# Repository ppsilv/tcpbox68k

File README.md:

## tcpbox68k
This is my MC68000 first project.

# Computer.

The idea behind this project is to develog a minicomputer as if I was in 1980.
I will try to use chips of that era except for memory because the memories of
that time were small in storage quantity.

I know that a concept of a minicomputer is not an exact science, so it is not
easy to reach a consensus on the subject, so I will use a definition that I found
very pertinent at the time of the reign of minicomputers. Since data storage
and memory were very expensive at that time, a minicomputer for its price had
to have many of these components.

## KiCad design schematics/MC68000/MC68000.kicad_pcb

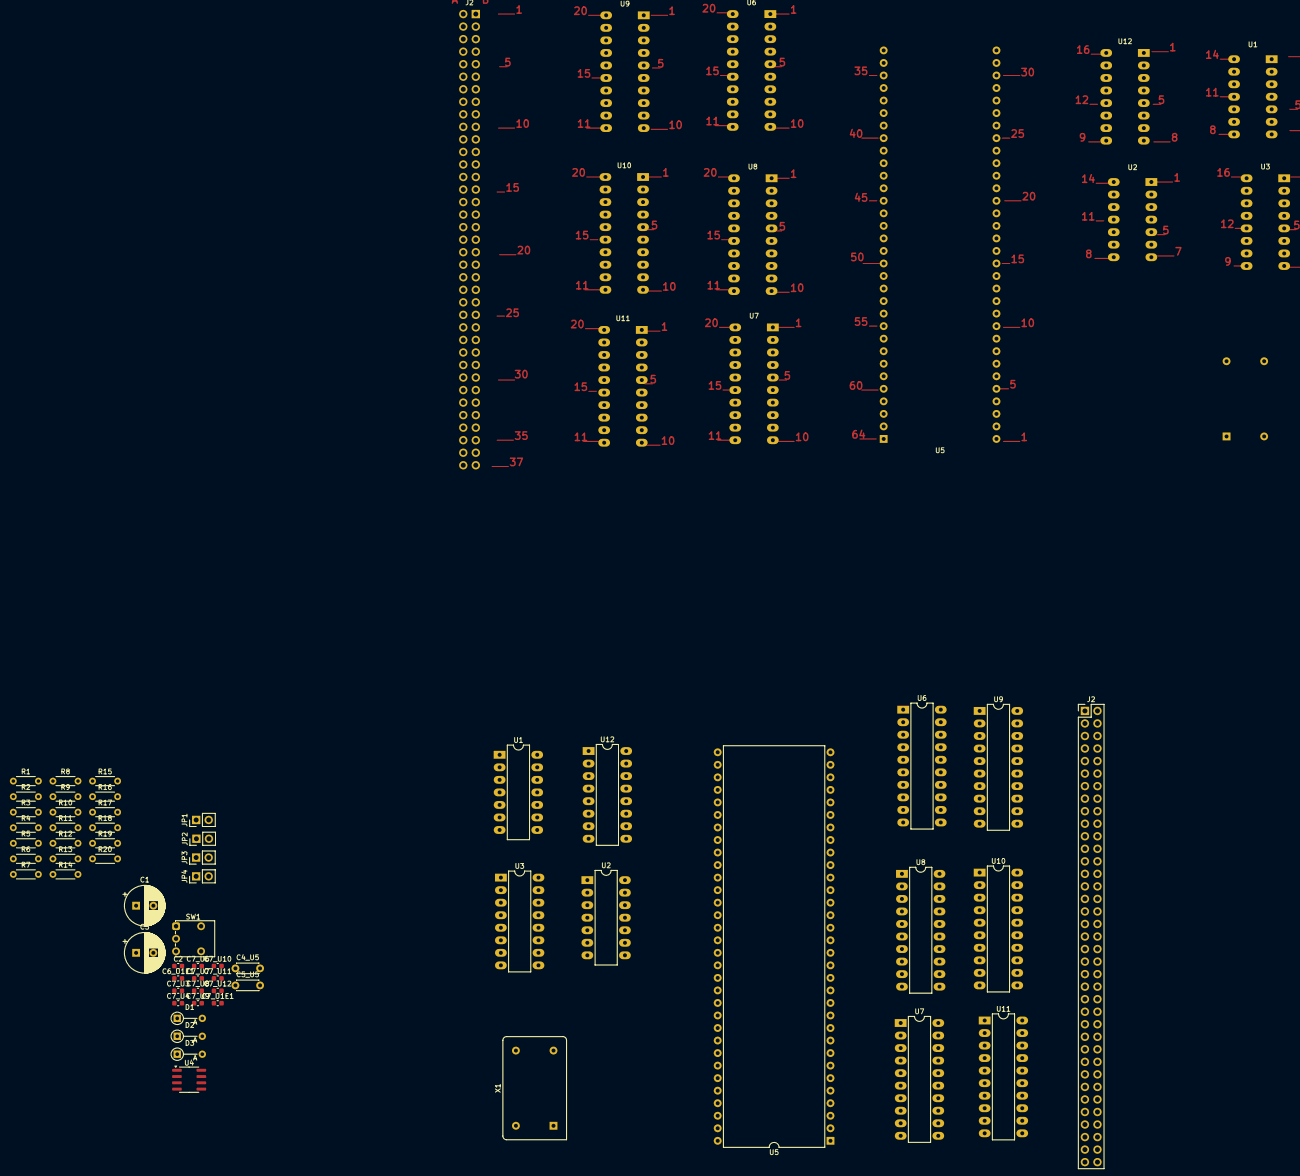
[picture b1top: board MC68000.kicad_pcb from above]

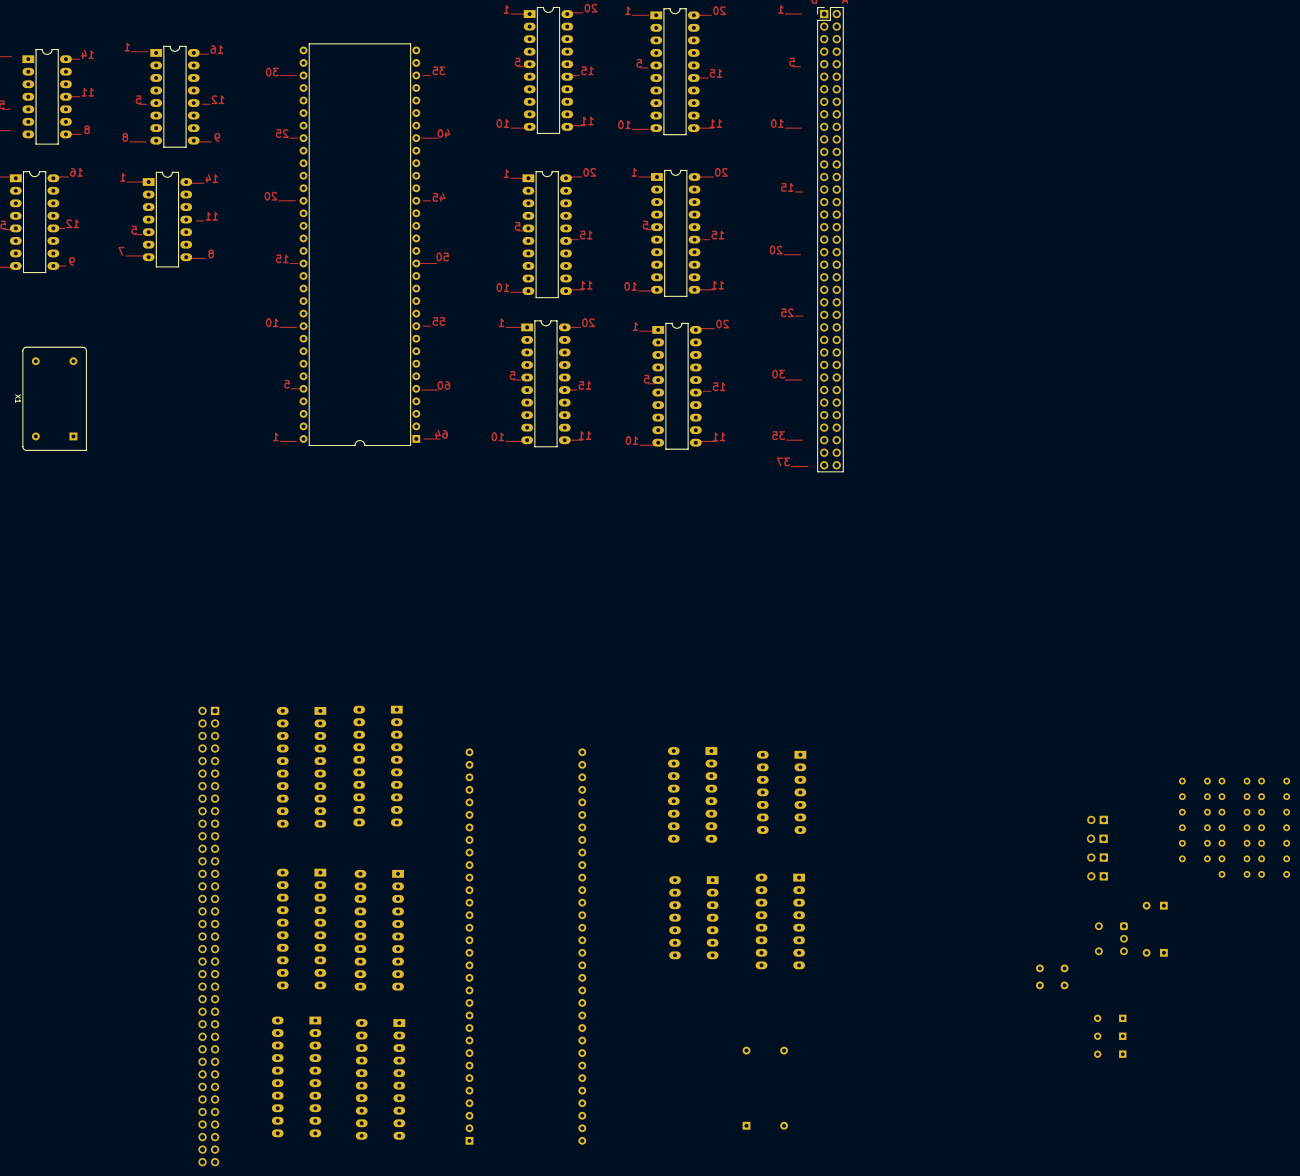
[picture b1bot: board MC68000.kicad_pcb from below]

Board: 2 copper layers, 71 parts (13 on the bottom side), 138 nets, no tracks yet.

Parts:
C1, C3: 1uf; CP_Radial_D8.0mm_P3.50mm
C2: 10nF; C_0603_1608Metric
C4_U5, C5_U5: 100nF; C_Disc_D4.3mm_W1.9mm_P5.00mm
C6_U1E1, C7_U1E1, C7_U3, C7_U4, C7_U6, C7_U7, C7_U8, C7_U9, C7_U10, C7_U11, C7_U12: 100nF; C_0603_1608Metric
D1: /RESET; D_DO-34_SOD68_P5.08mm_Vertical_AnodeUp
D2: /HALT; D_DO-34_SOD68_P5.08mm_Vertical_AnodeUp
D3: ON; D_DO-34_SOD68_P5.08mm_Vertical_AnodeUp
J2, J2#2: Conn_02x37_Row_Letter_Last; PinHeader_2x37_P2.54mm_Vertical
JP1, JP2: Jumper_2_Bridged; PinHeader_1x02_P2.54mm_Vertical
JP3, JP4: Jumper_2_Open; PinHeader_1x02_P2.54mm_Vertical
R1, R2, R3, R4, R7, R8, R9, R10, R11, R12, R13, R14, R15, R17: 10k; R_Axial_DIN0204_L3.6mm_D1.6mm_P5.08mm_Horizontal
R5, R6: 270k; R_Axial_DIN0204_L3.6mm_D1.6mm_P5.08mm_Horizontal
R16: 4K7; R_Axial_DIN0204_L3.6mm_D1.6mm_P5.08mm_Horizontal
R18, R19, R20: 470R; R_Axial_DIN0204_L3.6mm_D1.6mm_P5.08mm_Horizontal
SW1: Reset; SW_Push_1P2T_Vertical_E-Switch_800UDP8P1A1M6
U1, U1#2: 74LS00; CERDIP-14_W7.62mm_SideBrazed_LongPads
U2, U2#2: 74LS05; CERDIP-14_W7.62mm_SideBrazed_LongPads
U3, U3#2: 74LS161; CERDIP-16_W7.62mm_SideBrazed_LongPads
U4: ICM7555xB; SOIC-8_3.9x4.9mm_P1.27mm
U5, U5#2: 68000D; DIP-64_W22.86mm
U6, U6#2, U9, U9#2, U10, U10#2, U11, U11#2: 74LS244; CERDIP-20_W7.62mm_SideBrazed_LongPads
U7, U7#2, U8, U8#2: 74LS245; CERDIP-20_W7.62mm_SideBrazed_LongPads
U12, U12#2: 74LS148; CERDIP-16_W7.62mm_SideBrazed_LongPads
X1, X1#2: 16Mhz; Oscillator_DIP-14

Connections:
+5V: C4_U5.1, C5_U5.1, D1.1 (K), D2.1 (K), D3.1 (K), R1.1, R2.1, R3.1, R4.1, R5.1, R6.1, R7.1, R8.1, R9.1, R10.1, R11.1, R12.1, R13.1, R14.1, R15.1, R16.1, R17.1, U3.1 (~MR), U3.10 (CET), U3.16 (VCC), U3#2.1 (~MR), U3#2.10 (CET), U3#2.16 (VCC), U4.4 (R), U4.8 (VCC), U5.14 (VCC), U5.49 (VCC), U5#2.14 (VCC), U5#2.49 (VCC), U6.20 (VCC), U6#2.20 (VCC), U7.20 (VCC), U7#2.20 (VCC), U8.20 (VCC), U8#2.20 (VCC), U9.20 (VCC), U9#2.20 (VCC), U10.20 (VCC), U10#2.20 (VCC), U11.20 (VCC), U11#2.20 (VCC), U12.16 (VCC), U12#2.16 (VCC), X1.14 (Vcc), X1#2.14 (Vcc)
/CPU/D0: U5.5 (D0), U5#2.5 (D0), U7.18 (B0), U7#2.18 (B0)
/CPU/D1: U5.4 (D1), U5#2.4 (D1), U7.17 (B1), U7#2.17 (B1)
/CPU/D2: U5.3 (D2), U5#2.3 (D2), U7.16 (B2), U7#2.16 (B2)
/CPU/D3: U5.2 (D3), U5#2.2 (D3), U7.15 (B3), U7#2.15 (B3)
/CPU/D4: U5.1 (D4), U5#2.1 (D4), U7.14 (B4), U7#2.14 (B4)
/CPU/D5: U5.64 (D5), U5#2.64 (D5), U7.13 (B5), U7#2.13 (B5)
/CPU/D6: U5.63 (D6), U5#2.63 (D6), U7.12 (B6), U7#2.12 (B6)
/CPU/D7: U5.62 (D7), U5#2.62 (D7), U7.11 (B7), U7#2.11 (B7)
/CPU/D8: U5.61 (D8), U5#2.61 (D8), U8.18 (B0), U8#2.18 (B0)
/CPU/D9: U5.60 (D9), U5#2.60 (D9), U8.17 (B1), U8#2.17 (B1)
/CPU/D10: U5.59 (D10), U5#2.59 (D10), U8.16 (B2), U8#2.16 (B2)
/CPU/D11: U5.58 (D11), U5#2.58 (D11), U8.15 (B3), U8#2.15 (B3)
/CPU/D12: U5.57 (D12), U5#2.57 (D12), U8.14 (B4), U8#2.14 (B4)
/CPU/D13: U5.56 (D13), U5#2.56 (D13), U8.13 (B5), U8#2.13 (B5)
/CPU/D14: U5.55 (D14), U5#2.55 (D14), U8.12 (B6), U8#2.12 (B6)
/CPU/D15: U5.54 (D15), U5#2.54 (D15), U8.11 (B7), U8#2.11 (B7)
/CPU/FC0: U5.28 (FC0), U5#2.28 (FC0), U6.11 (I0b), U6#2.11 (I0b)
/CPU/FC1: U5.27 (FC1), U5#2.27 (FC1), U6.13 (I1b), U6#2.13 (I1b)
/CPU/FC2: U5.26 (FC2), U5#2.26 (FC2), U6.15 (I2b), U6#2.15 (I2b)
/CPU/IPL0: R15.2, U5.25 (IPL0), U5#2.25 (IPL0), U12.9 (S0), U12#2.9 (S0)
/CPU/IPL1: R14.2, U5.24 (IPL1), U5#2.24 (IPL1), U12.7 (S1), U12#2.7 (S1)
/CPU/IPL2: R13.2, U5.23 (IPL2), U5#2.23 (IPL2), U12.6 (S2), U12#2.6 (S2)
/CPU/IRQ1: U12.11 (I1), U12#2.11 (I1)
/CPU/IRQ2: U12.12 (I2), U12#2.12 (I2)
/CPU/IRQ3: U12.13 (I3), U12#2.13 (I3)
/CPU/IRQ4: U12.1 (I4), U12#2.1 (I4)
/CPU/IRQ5: U12.2 (I5), U12#2.2 (I5)
/CPU/IRQ6: U12.3 (I6), U12#2.3 (I6)
/CPU/IRQ7: U12.4 (I7), U12#2.4 (I7)
/CPU/LDS: U5.8 (LDS), U5#2.8 (LDS)
/CPU/R/W: U5.9 (R/W), U5#2.9 (R/W), U6.17 (I3b), U6#2.17 (I3b), U7.1 (A->B), U7#2.1 (A->B), U8.1 (A->B), U8#2.1 (A->B)
/CPU/UDS: U5.7 (UDS), U5#2.7 (UDS)
/CPU/addr1: U5.29 (A1), U5#2.29 (A1), U9.2 (I0a), U9#2.2 (I0a)
/CPU/addr2: U5.30 (A2), U5#2.30 (A2), U9.4 (I1a), U9#2.4 (I1a)
/CPU/addr3: U5.31 (A3), U5#2.31 (A3), U9.6 (I2a), U9#2.6 (I2a)
/CPU/addr4: U5.32 (A4), U5#2.32 (A4), U9.8 (I3a), U9#2.8 (I3a)
/CPU/addr5: U5.33 (A5), U5#2.33 (A5), U9.11 (I0b), U9#2.11 (I0b)
/CPU/addr6: U5.34 (A6), U5#2.34 (A6), U9.13 (I1b), U9#2.13 (I1b)
/CPU/addr7: U5.35 (A7), U5#2.35 (A7), U9.15 (I2b), U9#2.15 (I2b)
/CPU/addr8: U5.36 (A8), U5#2.36 (A8), U9.17 (I3b), U9#2.17 (I3b)
/CPU/addr9: U5.37 (A9), U5#2.37 (A9), U10.2 (I0a), U10#2.2 (I0a)
/CPU/addr10: U5.38 (A10), U5#2.38 (A10), U10.4 (I1a), U10#2.4 (I1a)
/CPU/addr11: U5.39 (A11), U5#2.39 (A11), U10.6 (I2a), U10#2.6 (I2a)
/CPU/addr12: U5.40 (A12), U5#2.40 (A12), U10.8 (I3a), U10#2.8 (I3a)
/CPU/addr13: U5.41 (A13), U5#2.41 (A13), U10.11 (I0b), U10#2.11 (I0b)
/CPU/addr14: U5.42 (A14), U5#2.42 (A14), U10.13 (I1b), U10#2.13 (I1b)
/CPU/addr15: U5.43 (A15), U5#2.43 (A15), U10.15 (I2b), U10#2.15 (I2b)
/CPU/addr16: U5.44 (A16), U5#2.44 (A16), U10.17 (I3b), U10#2.17 (I3b)
/CPU/addr17: U5.45 (A17), U5#2.45 (A17), U11.2 (I0a), U11#2.2 (I0a)
/CPU/addr18: U5.46 (A18), U5#2.46 (A18), U11.4 (I1a), U11#2.4 (I1a)
/CPU/addr19: U5.47 (A19), U5#2.47 (A19), U11.6 (I2a), U11#2.6 (I2a)
/CPU/addr20: U5.48 (A20), U5#2.48 (A20), U11.8 (I3a), U11#2.8 (I3a)
/CPU/addr21: U5.50 (A21), U5#2.50 (A21), U11.11 (I0b), U11#2.11 (I0b)
/CPU/addr22: U5.51 (A22), U5#2.51 (A22), U11.13 (I1b), U11#2.13 (I1b)
/CPU/addr23: U5.52 (A23), U5#2.52 (A23), U11.15 (I2b), U11#2.15 (I2b)
/CPU/bA1: U9.18 (O0a), U9#2.18 (O0a)
/CPU/bA2: U9.16 (O1a), U9#2.16 (O1a)
/CPU/bA3: U9.14 (O2a), U9#2.14 (O2a)
/CPU/bA4: U9.12 (O3a), U9#2.12 (O3a)
/CPU/bA5: U9.9 (O0b), U9#2.9 (O0b)
/CPU/bA6: U9.7 (O1b), U9#2.7 (O1b)
/CPU/bA7: U9.5 (O2b), U9#2.5 (O2b)
/CPU/bA8: U9.3 (O3b), U9#2.3 (O3b)
/CPU/bA9: U10.18 (O0a), U10#2.18 (O0a)
/CPU/bA10: U10.16 (O1a), U10#2.16 (O1a)
/CPU/bA11: U10.14 (O2a), U10#2.14 (O2a)
/CPU/bA12: U10.12 (O3a), U10#2.12 (O3a)
/CPU/bA13: U10.9 (O0b), U10#2.9 (O0b)
/CPU/bA14: U10.7 (O1b), U10#2.7 (O1b)
/CPU/bA15: U10.5 (O2b), U10#2.5 (O2b)
/CPU/bA16: U10.3 (O3b), U10#2.3 (O3b)
/CPU/bA17: U11.18 (O0a), U11#2.18 (O0a)
/CPU/bA18: U11.16 (O1a), U11#2.16 (O1a)
/CPU/bA19: U11.14 (O2a), U11#2.14 (O2a)
/CPU/bA20: U11.12 (O3a), U11#2.12 (O3a)
/CPU/bA21: U11.9 (O0b), U11#2.9 (O0b)
/CPU/bA22: U11.7 (O1b), U11#2.7 (O1b)
/CPU/bA23: U11.5 (O2b), U11#2.5 (O2b)
/CPU/bD0: U7.2 (A0), U7#2.2 (A0)
/CPU/bD1: U7.3 (A1), U7#2.3 (A1)
/CPU/bD2: U7.4 (A2), U7#2.4 (A2)
/CPU/bD3: U7.5 (A3), U7#2.5 (A3)
/CPU/bD4: U7.6 (A4), U7#2.6 (A4)
/CPU/bD5: U7.7 (A5), U7#2.7 (A5)
/CPU/bD6: U7.8 (A6), U7#2.8 (A6)
/CPU/bD7: U7.9 (A7), U7#2.9 (A7)
/CPU/bD8: U8.2 (A0), U8#2.2 (A0)
/CPU/bD9: U8.3 (A1), U8#2.3 (A1)
/CPU/bD10: U8.4 (A2), U8#2.4 (A2)
/CPU/bD11: U8.5 (A3), U8#2.5 (A3)
/CPU/bD12: U8.6 (A4), U8#2.6 (A4)
/CPU/bD13: U8.7 (A5), U8#2.7 (A5)
/CPU/bD14: U8.8 (A6), U8#2.8 (A6)
/CPU/bD15: U8.9 (A7), U8#2.9 (A7)
/CPU/bE: U6.12 (O3a), U6#2.12 (O3a)
/CPU/bFC0: U6.9 (O0b), U6#2.9 (O0b)
/CPU/bFC1: U6.7 (O1b), U6#2.7 (O1b)
/CPU/bFC2: U6.5 (O2b), U6#2.5 (O2b)
/CPU/bR/W: U6.3 (O3b), U6#2.3 (O3b)
/CPU//AS: U5.6 (AS), U5#2.6 (AS), U11.17 (I3b), U11#2.17 (I3b)
/CPU//BERR: R7.2, U5.22 (BERR), U5#2.22 (BERR)
/CPU//BG: U5.11 (BG), U5#2.11 (BG)
/CPU//BGACK: R12.2, U2.5, U2#2.5, U5.12 (BGACK), U5#2.12 (BGACK)
/CPU//BR: R10.2, U5.13 (BR), U5#2.13 (BR)
/CPU//DTACK: R17.2, U3.11 (Q3), U3#2.11 (Q3), U5.10 (DTACK), U5#2.10 (DTACK)
/CPU//E: U5.20 (E), U5#2.20 (E), U6.8 (I3a), U6#2.8 (I3a)
/CPU//HALT: R11.2, U2.4, U2.9, U2#2.4, U2#2.9, U5.17 (HALT), U5#2.17 (HALT)
/CPU//LDS: U6.4 (I1a), U6#2.4 (I1a)
/CPU//RESET: R9.2, R18.2, U2.2, U2#2.2, U5.18 (RESET), U5#2.18 (RESET)
/CPU//UDS: U6.2 (I0a), U6#2.2 (I0a)
/CPU//VMA: U5.19 (VMA), U5#2.19 (VMA), U6.6 (I2a), U6#2.6 (I2a)
/CPU//VPA: R8.2, U5.21 (VPA), U5#2.21 (VPA)
/CPU//bAS: U11.3 (O3b), U11#2.3 (O3b)
/CPU//bLDS: U6.16 (O1a), U6#2.16 (O1a)
/CPU//bUDS: U6.18 (O0a), U6#2.18 (O0a)
/CPU//bVMA: U6.14 (O2a), U6#2.14 (O2a)
CLK: U3.2 (CP), U3#2.2 (CP)
GND: C1.2, C2.2, C3.2, C4_U5.2, C5_U5.2, JP1.1 (A), JP2.1 (A), JP3.1 (A), JP4.1 (A), R20.2, SW1.1, U3.8 (GND), U3#2.8 (GND), U4.1 (GND), U5.16 (GND), U5.53 (GND), U5#2.16 (GND), U5#2.53 (GND), U6.10 (GND), U6#2.10 (GND), U7.10 (GND), U7.19 (CE), U7#2.10 (GND), U7#2.19 (CE), U8.10 (GND), U8.19 (CE), U8#2.10 (GND), U8#2.19 (CE), U9.10 (GND), U9#2.10 (GND), U10.10 (GND), U10#2.10 (GND), U11.10 (GND), U11#2.10 (GND), U12.5 (EI), U12.8 (GND), U12.10 (IO), U12#2.5 (EI), U12#2.8 (GND), U12#2.10 (IO), X1.7 (GND), X1#2.7 (GND)
unnamed: D1.2 (A), R18.1
unnamed: D2.2 (A), R19.1
unnamed: D3.2 (A), R20.1
unnamed: JP1.2 (B), R1.2, U3.3 (D0), U3#2.3 (D0)
unnamed: JP2.2 (B), R2.2, U3.4 (D1), U3#2.4 (D1)
unnamed: JP3.2 (B), R3.2, U3.5 (D2), U3#2.5 (D2)
unnamed: JP4.2 (B), R4.2, U3.6 (D3), U3#2.6 (D3)
unnamed: R19.2, U2.8, U2#2.8
unnamed: C6_U1E1.2, C7_U1E1.2, C7_U3.2, C7_U4.2, C7_U6.2, C7_U7.2, C7_U8.2, C7_U9.2, C7_U10.2, C7_U11.2, C7_U12.2, U1.7 (GND), U1#2.7 (GND), U2.7 (GND), U2#2.7 (GND)
unnamed: C6_U1E1.1, C7_U1E1.1, C7_U3.1, C7_U4.1, C7_U6.1, C7_U7.1, C7_U8.1, C7_U9.1, C7_U10.1, C7_U11.1, C7_U12.1, U1.14 (VCC), U1#2.14 (VCC), U2.14 (VCC), U2#2.14 (VCC)
unnamed: U1.3, U1#2.3, U3.7 (CEP), U3.9 (~PE), U3#2.7 (CEP), U3#2.9 (~PE)
unnamed: C2.1, U4.5 (CV)
unnamed: C3.1, R6.2, U4.6 (THR), U4.7 (DIS)
unnamed: U2.1, U2.3, U2#2.1, U2#2.3, U4.3 (Q)
unnamed: C1.1, R5.2, SW1.2, U4.2 (TR)
unnamed: U5.15 (CLK), U5#2.15 (CLK), X1.8 (OUT), X1#2.8 (OUT)
unnamed: R16.2, U2.6, U2#2.6, U6.1 (OEa), U6.19 (OEb), U6#2.1 (OEa), U6#2.19 (OEb), U9.1 (OEa), U9.19 (OEb), U9#2.1 (OEa), U9#2.19 (OEb), U10.1 (OEa), U10.19 (OEb), U10#2.1 (OEa), U10#2.19 (OEb), U11.1 (OEa), U11.19 (OEb), U11#2.1 (OEa), U11#2.19 (OEb)
/RAM_CS: U1.2, U1#2.2
/ROM_CE: U1.1, U1#2.1

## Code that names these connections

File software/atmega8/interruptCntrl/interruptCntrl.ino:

#include <avr/io.h>
#include <util/atomic.h>
#include <util/delay.h>

//When cpu say FC0,FC1 and FC2  = 1,1,1 but no interrupt active.
#define CPU_INT_ACK_WRONG     0x80
//When arrive a irq resquest but we have one active irq in curse
#define IRQ_REQUEST_LOST      0x81
//ACK sem interrupção
#define ACK_WITHOUT_INT       0x82
//Irq <level> must be released
#define IRQ_MUST_BE_RELEASED  0x83

// Definições dos pinos IPL no PORTB
#define IPL0  PC0
#define IPL1  PC1  
#define IPL2  PC2
#define IPL_MASK ((1 << IPL0) | (1 << IPL1) | (1 << IPL2))

// Definições dos pinos de IRQ no PORTD
#define IRQ1_PIN  PD2
#define IRQ2_PIN  PD3
#define IRQ3_PIN  PD4
#define IRQ4_PIN  PD5
#define IRQ5_PIN  PD6
#define IRQ7_PIN  PD7
#define ALL_IRQ_MASK ((1<<IRQ1_PIN)|(1<<IRQ2_PIN)|(1<<IRQ3_PIN)|(1<<IRQ4_PIN)|(1<<IRQ5_PIN)|(1<<IRQ7_PIN))

#define TIMEOUT  1000
long timer1=millis()+100;
long timer2=millis()+TIMEOUT;

#define NOT_ACTIVE 7
unsigned char irq_s[8]={NOT_ACTIVE,NOT_ACTIVE,NOT_ACTIVE,NOT_ACTIVE,NOT_ACTIVE,NOT_ACTIVE,NOT_ACTIVE,NOT_ACTIVE};
// Variáveis globais
volatile uint8_t active_irq = NOT_ACTIVE;

#define LED_PIN PB5  // Exemplo: LED no PB5 (ajuste conforme seu hardware)
#define LED_PORT PORTB

// Configuração dos ports
void setup_ports() {
    // Configurar PB0-PB2 como saídas (IPL0-IPL2) + VPA_PIN
    DDRC |= (1 << IPL0) | (1 << IPL1) | (1 << IPL2) ;
    // VPA inicialmente inativo    
    PORTC |=  (1 << IPL0) | (1 << IPL1) | (1 << IPL2) ;  
    
    // Configurar PB1 como saída (OC1A - Debug) LED
    DDRB |= (1 << PB1)|(1 << PB5)  ;

    // Configura PD0-PD5 como entradas com pull-up
    DDRD &= ~ALL_IRQ_MASK;
    PORTD |= ALL_IRQ_MASK;    
}

void setup_timer1() {
    TCCR1A = (1 << COM1A0);    // Toggle OC1A on compare match
    TCCR1B = (1 << WGM12) | (1 << CS11);  // CTC mode, prescaler 8
    OCR1A = 500;              // 1ms period
    TIMSK |= (1 << OCIE1A);    // Habilitar interrupção
}

volatile uint32_t ms_counter = 0;

ISR(TIMER1_COMPA_vect) {
  ms_counter++;
  //start_irq(1);  // Gera IRQ nível 6
}

void setup_timer2() {  // ATMega8 usa Timer2, não Timer0
    // Configurar Timer2 para CTC mode
    TCCR2 = (1 << WGM21);              // CTC mode
    OCR2 = 78;                         // 50us @ 16MHz/8
    TCCR2 |= (1 << CS21);              // Prescaler 8
    TIMSK |= (1 << OCIE2);             // Enable interrupt
}

ISR(TIMER2_COMP_vect) {

}
void setup_fc_interrupt() {
    // Configurar INT0 para FALLING EDGE (transição 1→0)
    MCUCR |= (1 << ISC01);      // Falling edge generates interrupt  
    MCUCR &= ~(1 << ISC00);     // Clear ISC00 bit
    GICR |= (1 << INT0);        // Enable INT0
}

ISR(INT0_vect) {
  irq_s[active_irq]=NOT_ACTIVE;
        __asm__ volatile("nop");   // +125ns - 1 ciclo
        __asm__ volatile("nop");   // +125ns - 1 ciclo  
        __asm__ volatile("nop");   // +125ns - 1 ciclo  
        __asm__ volatile("nop");   // +125ns - 1 ciclo
        __asm__ volatile("nop");   // +125ns - 1 ciclo  
        __asm__ volatile("nop");   // +125ns - 1 ciclo        
  PORTC = (PORTC & 0xF8);  //Limpa
  PORTC = PORTC | NOT_ACTIVE;   //seta
}

uint8_t check_irq_pins_status() {
    return (~PIND) & ALL_IRQ_MASK;
}



uint8_t get_irq_started() {
    uint8_t status = check_irq_pins_status();
    if (status & (1<<IRQ7_PIN)) return 0;
    if (status & (1<<IRQ5_PIN)) return 2;
    if (status & (1<<IRQ4_PIN)) return 3;
    if (status & (1<<IRQ3_PIN)) return 4;
    if (status & (1<<IRQ2_PIN)) return 5;
    if (status & (1<<IRQ1_PIN)) return 6;
    return NOT_ACTIVE;
}

// ✅ Função set_ipl CORRIGIDA
void set_ipl(uint8_t level) {
  level &= 0x07;
  //PORTC = (PORTC & 0xF8);  //Limpa 
  //PORTC = PORTC | level;   //seta
  PORTC = (PORTC & 0xF8) | level;  // Seta nível

  //      __asm__ volatile("nop");   // +125ns - 1 ciclo  
  //      __asm__ volatile("nop");   // +125ns - 1 ciclo
  //      __asm__ volatile("nop");   // +125ns - 1 ciclo  
  //      __asm__ volatile("nop");   // +125ns - 1 ciclo        
  //      __asm__ volatile("nop");   // +125ns - 1 ciclo  
  //      __asm__ volatile("nop");   // +125ns - 1 ciclo
  //      __asm__ volatile("nop");   // +125ns - 1 ciclo  
  //      __asm__ volatile("nop");   // +125ns - 1 ciclo        
  //      __asm__ volatile("nop");   // +125ns - 1 ciclo  
  //      __asm__ volatile("nop");   // +125ns - 1 ciclo
  //      __asm__ volatile("nop");   // +125ns - 1 ciclo  
  //      __asm__ volatile("nop");   // +125ns - 1 ciclo        
  // ⏰ Timing calibrado manualmente
    __asm__ volatile("nop\nnop\nnop\nnop\nnop\nnop\nnop\nnop\nnop\nnop\nnop\nnop");

  PORTC = (PORTC & 0xF8) | NOT_ACTIVE;  // Limpa ANTES do retrigger

  //PORTC = (PORTC & 0xF8);  //Limpa
  //PORTC = PORTC | NOT_ACTIVE;   //seta
  _delay_us(500);
  irq_s[active_irq]=NOT_ACTIVE;
  

}

void start_irq(uint8_t new_irq){
  if(new_irq == NOT_ACTIVE) return; //excesso de zelo quando estiver funcionando corretamente tirar isso daqui
  if (new_irq < 7 && irq_s[new_irq] == NOT_ACTIVE) {
    active_irq = new_irq;
    irq_s[active_irq]=active_irq;
    set_ipl(active_irq);
  }
}

void setup(){
  Serial.begin(9600);
  Serial.println("Teste do gerenciador de interrupção 1.0"); 
  setup_ports();

  //Setup interrups
  setup_timer1();
  //setup_timer2();

  sei();
  pinMode(LED_BUILTIN, OUTPUT);    
  timer1=millis()+TIMEOUT;
  //delay(5000); // 5 segundo
}


void loop() {

  while(1) {
    // 1️⃣ Verificação SÍNCRONA das IRQs
    start_irq(get_irq_started());

    //Activity led
    if ( (millis() > timer1) ){
      timer1=millis()+100;
      LED_PORT ^= (1 << LED_PIN);  // toggle LED
    }
  }
}

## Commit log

2025-07-04 Update...
2025-07-04 CPU schematic finished...
2025-07-09 cleanup zips and added memory map equations for pld
2025-07-12 added schemati for cpu without buffers
2025-07-13 Cpu's board tested
2025-07-14 Added test_led.asm
2025-07-16 remove doc dir
2025-07-17 update ebooks
2025-07-19 Monitor compiled success
2025-07-19 update makefile
2025-07-19 lib math added
2025-07-19 lib math removed
2025-07-21 update memoria rom executando codigo
2025-07-21 Leds blinking...
2025-07-22 Ram memory test 2 OK
2025-07-25 Uart reading writing with counter.asm
2025-07-25 Version 0.10 4 uarts running...
2025-07-25 Error's log updated...
2025-07-26 Compilando com linker
2025-07-28 Reading hexa values
2025-07-29 change bin name
2025-07-29 Build: 2025-07-29 17:28:19
2025-07-29 Update Makefile cosmetic things
2025-07-30 Terminal serial...
2025-07-31 Terminal serial
2025-08-01 Terminal totalmente debugado
2025-08-01 Refactoring of pdterm
2025-08-01 Sistem operating normal after refactoring
2025-08-01 Xmodem sending file
2025-08-02 Updating xmodem refactoring
2025-08-02 Develop xmodem 020825
2025-08-03 Esboço do xmodem no python pronto
2025-08-03 Updating...
2025-08-03 Refactoring: Serial rs232 code separated from PdTermPro
2025-08-03 Sending and receivin char from rs232
2025-08-07 finally thread_serial working 100%
2025-08-07 Solved o bug core dump...
2025-08-12 Uptloading program and running corretly via Xmodem with PdTermV1
2025-08-13 updating Makefile
2025-08-13 Versao 1.0
2025-08-13 UART new address 000
2025-08-13 monitor.bin filled to size 16384
2025-08-13 Rom checksum validating...
2025-08-13 flag program loaded
2025-08-13 Fixed bug in writeprogram
2025-08-13 Updating Readme...
2025-08-14 Now cpu writes single BYTES to memory...
2025-08-14 Now the GAL version gives 1Mbyte of SRAM access
2025-08-14 Update 2025/08/14
2025-08-14 Update 2025/08/14 17:00
2025-08-23 Interrupts working...
2025-08-23 Interrupts working update...
2025-08-26 Implementados Test_trap._asm Test_trap_c
2025-08-26 Trap 0 working to return to monitor
2025-08-27 added lib to compile applications
2025-08-27 Lib.. update
2025-08-27 tick 1ms running on int 6
2025-08-30 Atmega8 code completed
2025-09-01 Atmega8 firmware and schematics, ints working
2025-09-06 tinyBasic running
2025-09-06 peek and poke fixed
2025-09-07 peek,poke ok
2025-09-07 Master sincronized to stable-base
2025-09-07 while implemented
2025-09-07 Updating after code clean-up
2025-09-07 update..
2025-09-07 deleted software/TinybasicPlus
2025-09-07 added new version TinybasicPlus
2025-09-07 Implemented set baudrate
2026-03-21 Schematic update
2026-03-22 Implemented write screen via pico
2026-03-22 updating
2026-03-22 recolocando o monitor.asm
2026-03-22 card_vga com tratamento do lixo inicial no pi pico
2026-03-22 Tested D_RUN_CMD D_REG_X_LOW D_REG_Y_LOW CMD_SET_CUR_POS
2026-03-22 corrigido o bug troca de linha para Y + height
2026-03-22 corrigido o bug no posicionamento do cursor switch case sem break
2026-03-23 inserido comando vga set_txt_color no 68000
2026-03-24 Limpesa do codigo arquivos renomeados estrutura para font
2026-03-24 impl go home
2026-03-25 Clean up for 640x400 prepare of house to receive 320x200
2026-03-26 640p working and code fo 320p inserted and compiled together 640p
2026-03-26 640p working and code fo 320p fixed pio program names
2026-03-26 640p working updating
2026-03-26 Impl. 320x200
2026-03-27 vga mode changing well
2026-03-27 Finished video mode change 640p <-> 320p
2026-03-27 2026-03-27 updating
2026-03-27 2026-03-27 01 updating
2026-03-31 Added ch376s
2026-04-08 keyboard tests
2026-05-08 retornando para entes do ch376s
2026-05-10 fixed uart oscilator in schematic
2026-05-14 Added more apps to env68k
2026-05-14 De volta aos trilhos-2620
2026-05-21 Keyboard tested in dir apps/keyboard
